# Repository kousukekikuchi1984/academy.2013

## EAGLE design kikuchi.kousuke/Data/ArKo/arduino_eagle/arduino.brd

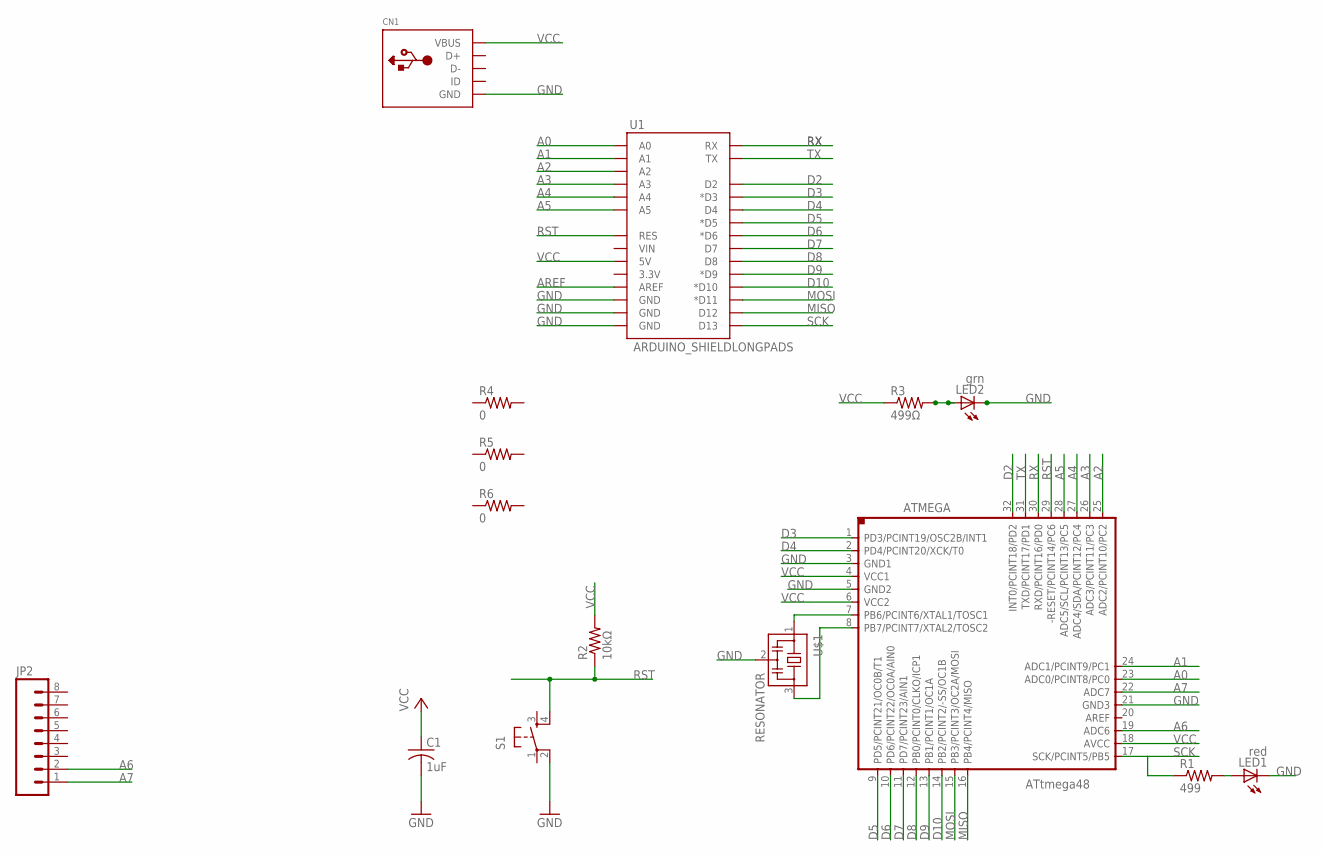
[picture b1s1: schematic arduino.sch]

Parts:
ATMEGA: 328p-au; TQFP32-08
C1: 1uF; C1206
CN1: USBMINIB; USB-MINIB
JP2: M08LOCK_LONGPADS; 1X08_LOCK_LONGPADS
LED1: red; CHIPLED_1206
LED2: grn; CHIPLED_1206
R1: 499; R1206
R2: 10kΩ; M1206
R3: 499Ω; M1206
R4, R5, R6: 0; M1206
S1: 6MM_SWITCH6MM_SWITCH; 6MM_SWITCH
U1: ARDUINO_SHIELDLONGPADS; DUEMILANOVE_SHIELD_LONGPADS
U$1: RESONATOR; EFOBM

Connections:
A0: ATMEGA.23 (ADC0/PCINT8/PC0), U1.A0
A1: ATMEGA.24 (ADC1/PCINT9/PC1), U1.A1
A2: ATMEGA.25 (ADC2/PCINT10/PC2), U1.A2
A3: ATMEGA.26 (ADC3/PCINT11/PC3), U1.A3
A4: ATMEGA.27 (ADC4/SDA/PCINT12/PC4), U1.A4
A5: ATMEGA.28 (ADC5/SCL/PCINT13/PC5), U1.A5
A6: ATMEGA.19 (ADC6), JP2.2
A7: ATMEGA.22 (ADC7), JP2.1
AREF: U1.AREF
D2: ATMEGA.32 (INT0/PCINT18/PD2), U1.D2
D3: ATMEGA.1 (PD3/PCINT19/OSC2B/INT1), U1.D3 (*D3)
D4: ATMEGA.2 (PD4/PCINT20/XCK/T0), U1.D4
D5: ATMEGA.9 (PD5/PCINT21/OC0B/T1), U1.D5 (*D5)
D6: ATMEGA.10 (PD6/PCINT22/OC0A/AIN0), U1.D6 (*D6)
D7: ATMEGA.11 (PD7/PCINT23/AIN1), U1.D7
D8: ATMEGA.12 (PB0/PCINT0/CLKO/ICP1), U1.D8
D9: ATMEGA.13 (PB1/PCINT1/OC1A), U1.D9 (*D9)
D10: ATMEGA.14 (PB2/PCINT2/-SS/OC1B), U1.D10 (*D10)
GND: ATMEGA.3 (GND1), ATMEGA.5 (GND2), ATMEGA.21 (GND3), C1.2, CN1.GND, LED1.C, LED2.C, S1.2 (P1), U1.GND@0 (GND), U1.GND@1 (GND), U1.GND@2 (GND), U$1.2
MISO: ATMEGA.16 (PB4/PCINT4/MISO), U1.D12
MOSI: ATMEGA.15 (PB3/PCINT3/OC2A/MOSI), U1.D11 (*D11)
unnamed: LED1.A, R1.2
unnamed: ATMEGA.7 (PB6/PCINT6/XTAL1/TOSC1), U$1.1
unnamed: ATMEGA.8 (PB7/PCINT7/XTAL2/TOSC2), U$1.3
unnamed: LED2.A, R3.2
RST: ATMEGA.29 (-RESET/PCINT14/PC6), R2.1, S1.4 (S1), U1.RES
RX: ATMEGA.30 (RXD/PCINT16/PD0), U1.RX
SCK: ATMEGA.17 (SCK/PCINT5/PB5), R1.1, U1.D13
TX: ATMEGA.31 (TXD/PCINT17/PD1), U1.TX
VCC: ATMEGA.4 (VCC1), ATMEGA.6 (VCC2), ATMEGA.18 (AVCC), C1.1, CN1.VBUS, R2.2, R3.1, U1.5V

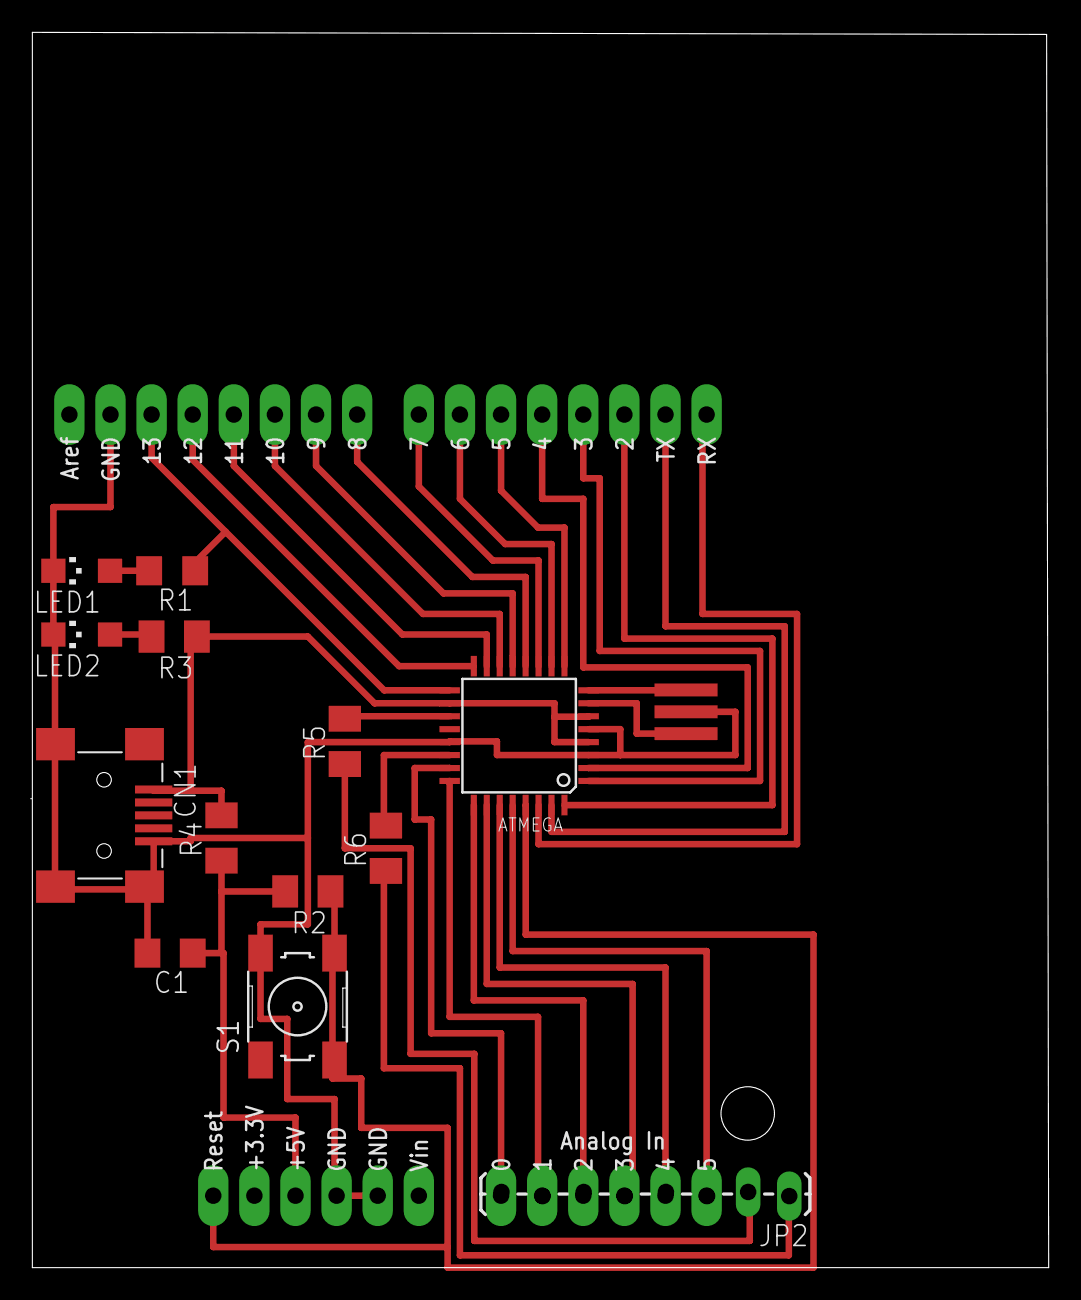
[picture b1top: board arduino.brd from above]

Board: 2 copper layers, 62.8 x 76.3 mm, 15 parts (0 on the bottom side), 29 nets.

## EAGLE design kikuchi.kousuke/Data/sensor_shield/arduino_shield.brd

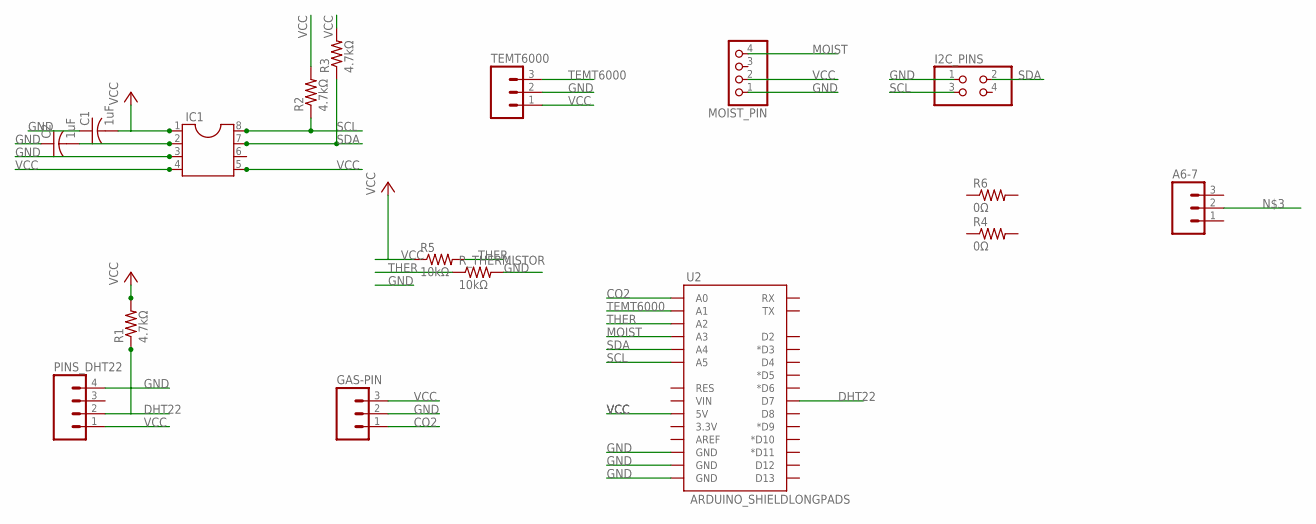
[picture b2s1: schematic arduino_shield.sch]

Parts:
A6-7: M03LOCK_LONGPADS; 1X03_LOCK_LONGPADS
C1, C2: 1uF; C1206
GAS-PIN: M03LOCK_LONGPADS; 1X03_LOCK_LONGPADS
I2C_PINS: PINHD-2X2; 2X02
IC1: DIL8S; SOCKET-08
MOIST_PIN: PINHD-1X4M; 1X04M
PINS_DHT22: M04LOCK_LONGPADS; 1X04_LOCK_LONGPADS
R1, R2, R3: 4.7kΩ; M1206
R4, R6: 0Ω; M1206
R5: 10kΩ; M1206
R_THERMISTOR: 10kΩ; M1206
TEMT6000: M03LOCK_LONGPADS; 1X03_LOCK_LONGPADS
U2: ARDUINO_SHIELDLONGPADS; DUEMILANOVE_SHIELD_LONGPADS

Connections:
CO2: GAS-PIN.1, U2.A0
DHT22: PINS_DHT22.2, R1.1, U2.D7
GND: C1.1, C2.1, GAS-PIN.2, I2C_PINS.1, IC1.3, MOIST_PIN.1, PINS_DHT22.4, R_THERMISTOR.2, TEMT6000.2, U2.GND@0 (GND), U2.GND@1 (GND), U2.GND@2 (GND)
MOIST: MOIST_PIN.4, U2.A3
unnamed: C2.2, IC1.2
SCL: I2C_PINS.3, IC1.8, R2.1, U2.A5
SDA: I2C_PINS.2, IC1.7, R3.1, U2.A4
TEMT6000: TEMT6000.3, U2.A1
THER: R5.2, R_THERMISTOR.1, U2.A2
VCC: C1.2, GAS-PIN.3, IC1.1, IC1.4, IC1.5, MOIST_PIN.2, PINS_DHT22.1, R1.2, R2.2, R3.2, R5.1, TEMT6000.1, U2.5V

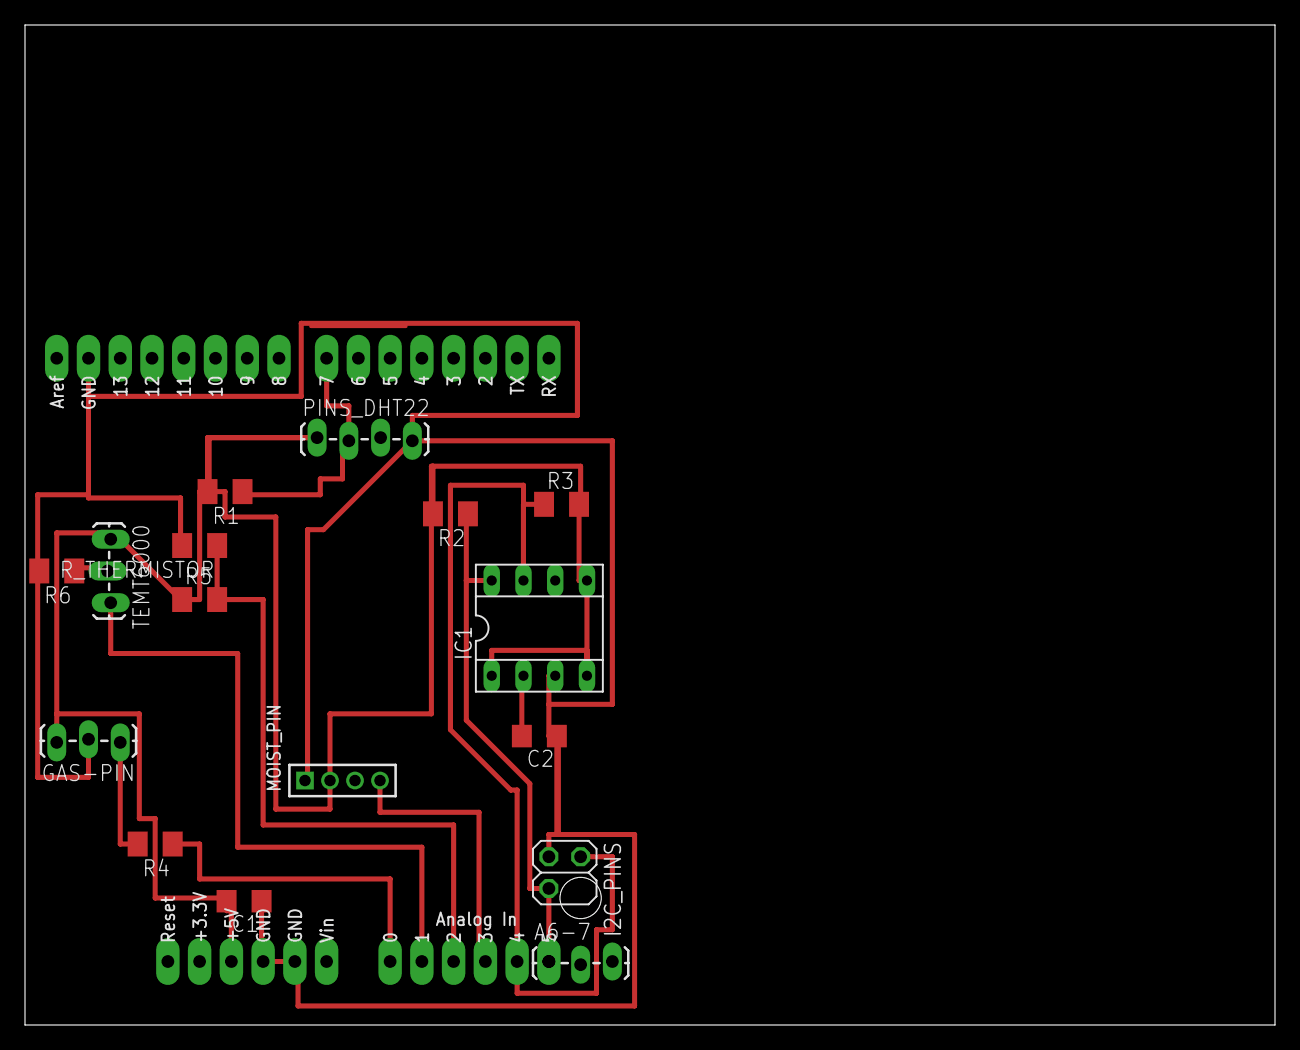
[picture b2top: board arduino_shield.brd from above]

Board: 2 copper layers, 100.0 x 80.0 mm, 17 parts (0 on the bottom side), 10 nets.

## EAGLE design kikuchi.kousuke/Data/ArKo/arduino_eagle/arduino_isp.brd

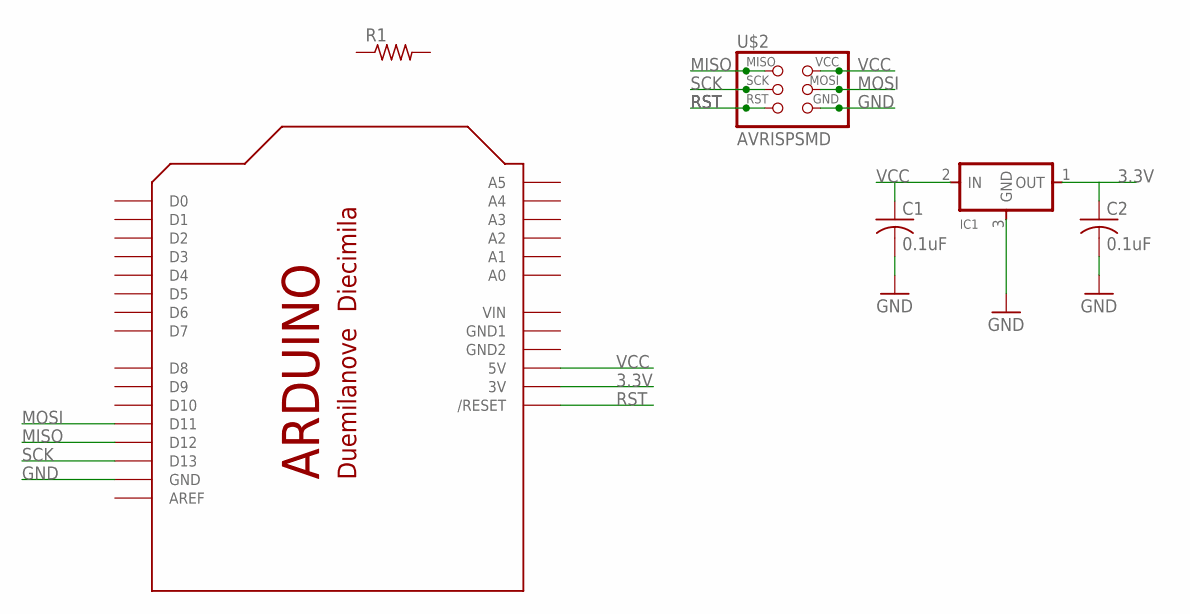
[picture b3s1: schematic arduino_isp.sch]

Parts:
C1, C2: 0.1uF; C1206
IC1: REGULATORSOT23; SOT23
R1: R-US_M1206; M1206
U$1: ARDUINODUEMILANOVE; ARDUINO
U$2: AVRISPSMD; 2X03SMD

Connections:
3.3V: C2.1, IC1.1 (OUT), U$1.3V
GND: C1.2, C2.2, IC1.3 (GND), U$1.GND, U$2.6 (GND)
GND1: U$1.GND1
GND2: U$1.GND2
MISO: U$1.D12, U$2.1 (MISO)
MOSI: U$1.D11, U$2.4 (MOSI)
RST: U$1.RESET (/RESET), U$2.5 (RST)
SCK: U$1.D13, U$2.3 (SCK)
VCC: C1.1, IC1.2 (IN), U$1.5V, U$2.2 (VCC)
VIN: U$1.VIN

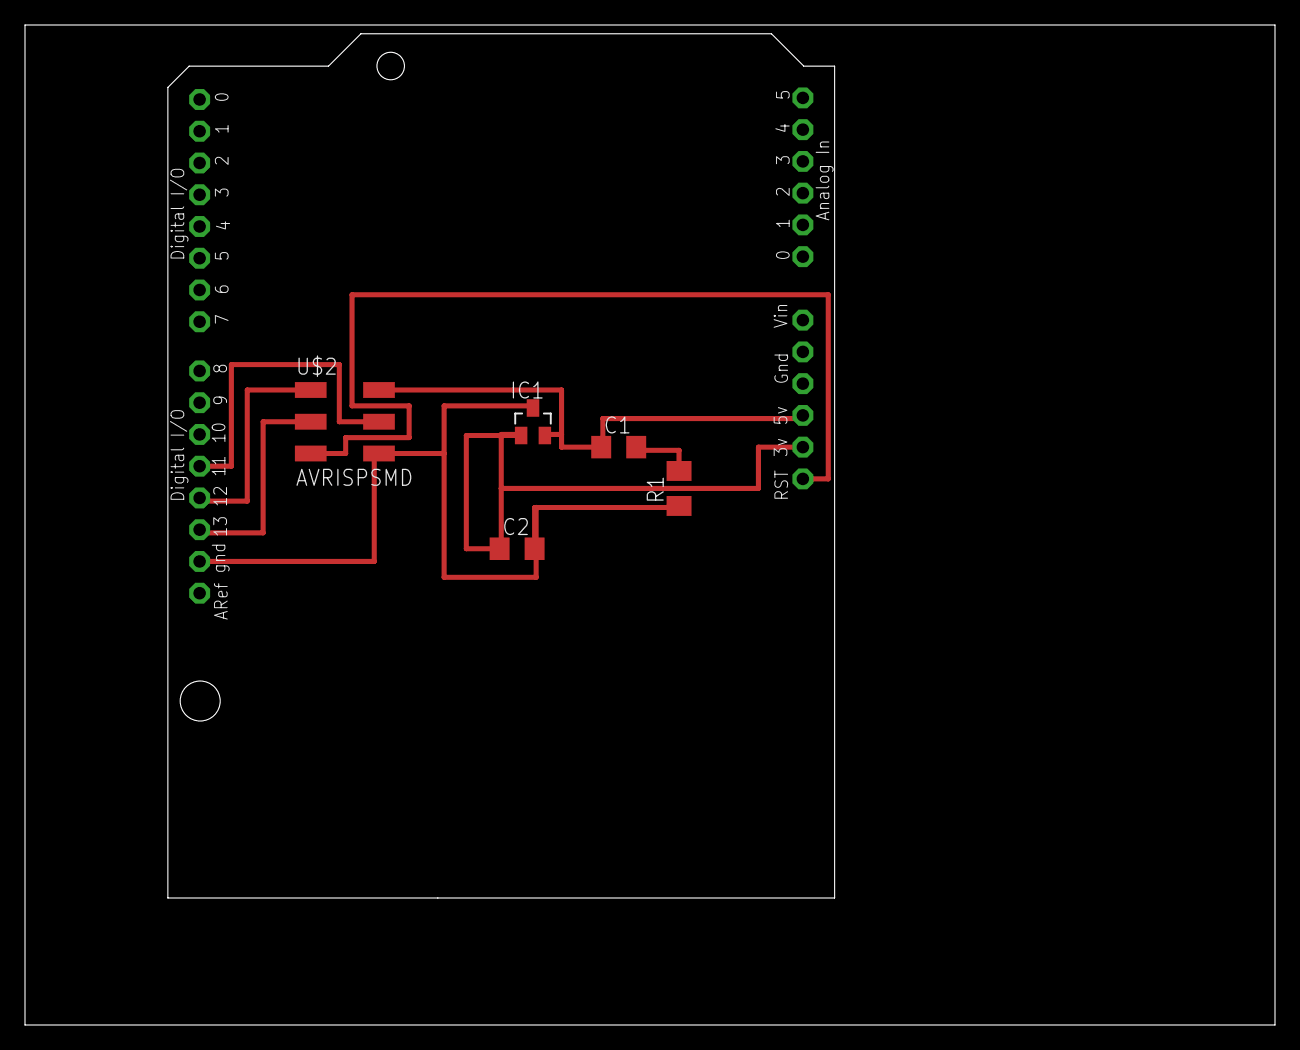
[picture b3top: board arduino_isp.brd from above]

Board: 2 copper layers, 100.0 x 80.0 mm, 6 parts (0 on the bottom side), 7 nets.

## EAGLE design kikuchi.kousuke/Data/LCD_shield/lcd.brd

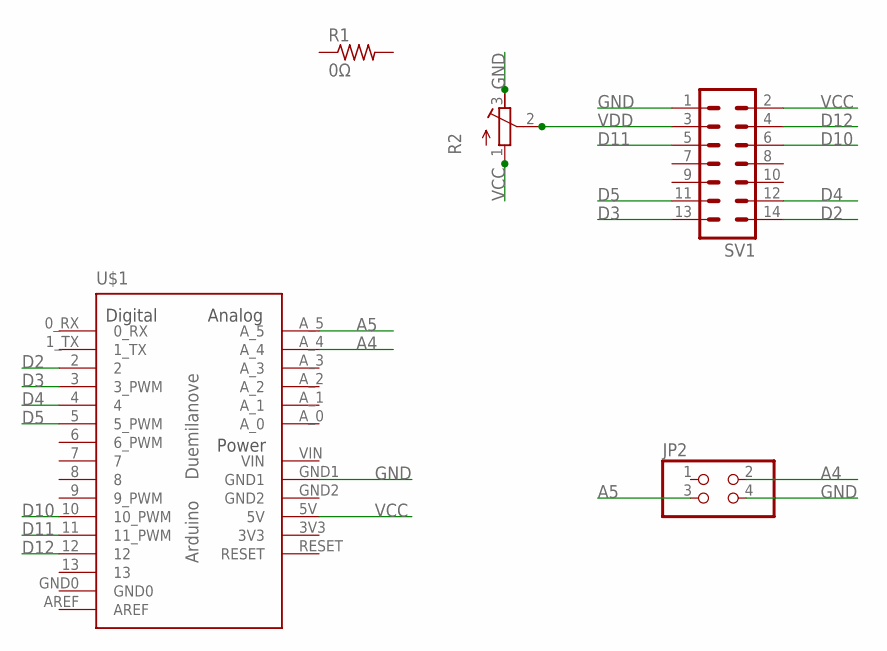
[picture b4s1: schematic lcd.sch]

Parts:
JP2: PINHD-2X2; 2X02
R1: 0Ω; M1206
R2: R-TRIMM5W; RTRIM5W
SV1: MA07-2
U$1: ARDUINO-USBLONG_PADS_TEXT; SHIELD

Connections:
3V3: U$1.3V3
A4: JP2.2, U$1.A_4
A5: JP2.3, U$1.A_5
D2: SV1.14, U$1.2
D3: SV1.13, U$1.3 (3_PWM)
D4: SV1.12, U$1.4
D5: SV1.11, U$1.5 (5_PWM)
D10: SV1.6, U$1.10 (10_PWM)
D11: SV1.5, U$1.11 (11_PWM)
D12: SV1.4, U$1.12
GND: JP2.4, R2.3 (E), SV1.1, U$1.GND1
VCC: R2.1 (A), SV1.2, U$1.5V
VDD: R2.2 (S), SV1.3
VIN: U$1.VIN

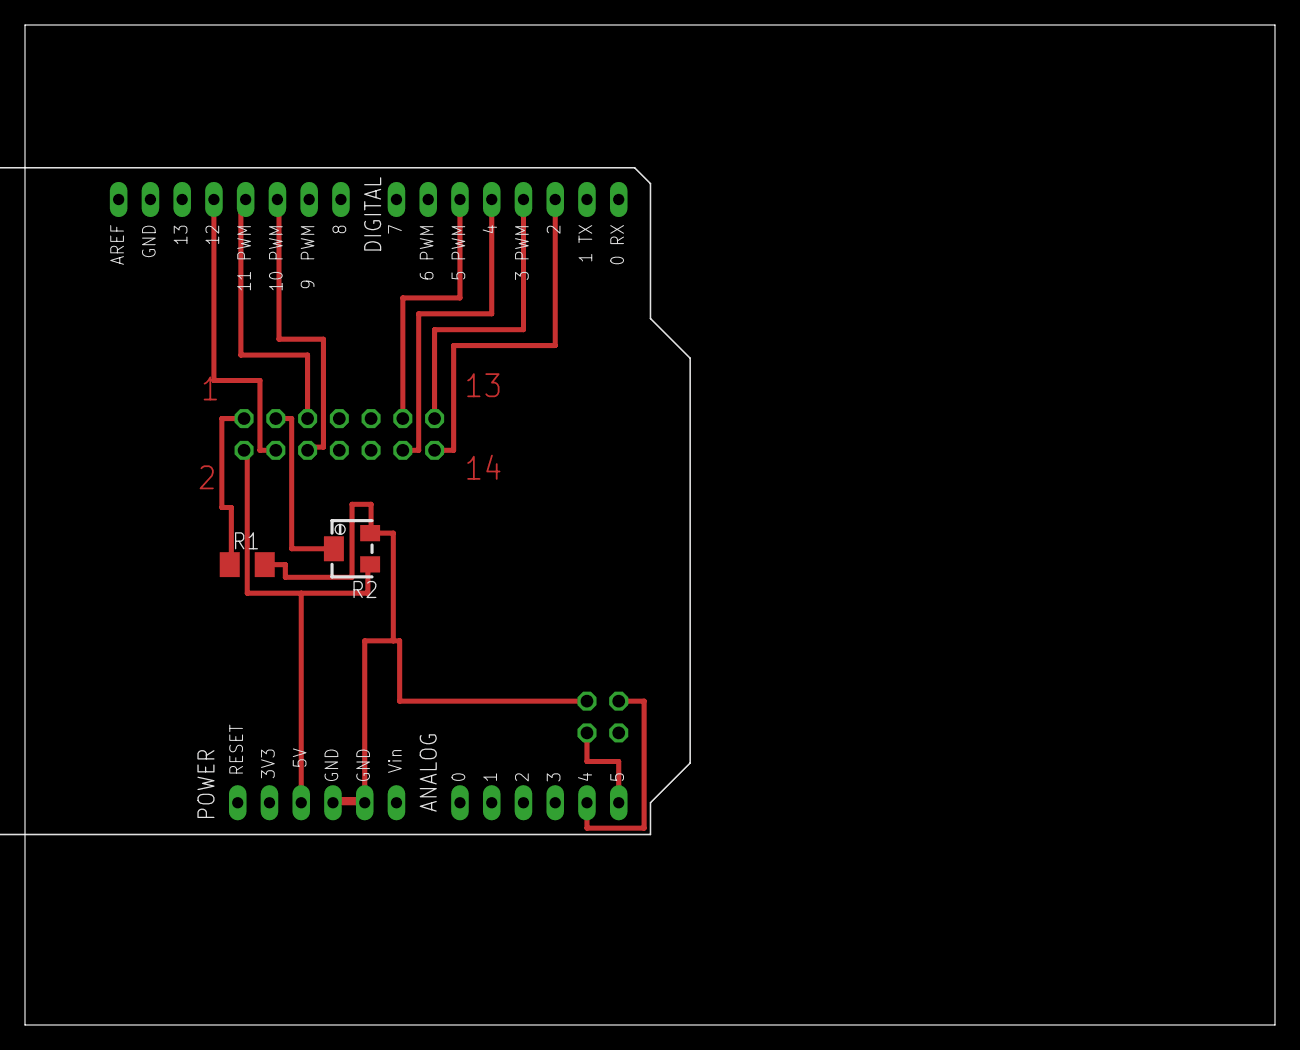
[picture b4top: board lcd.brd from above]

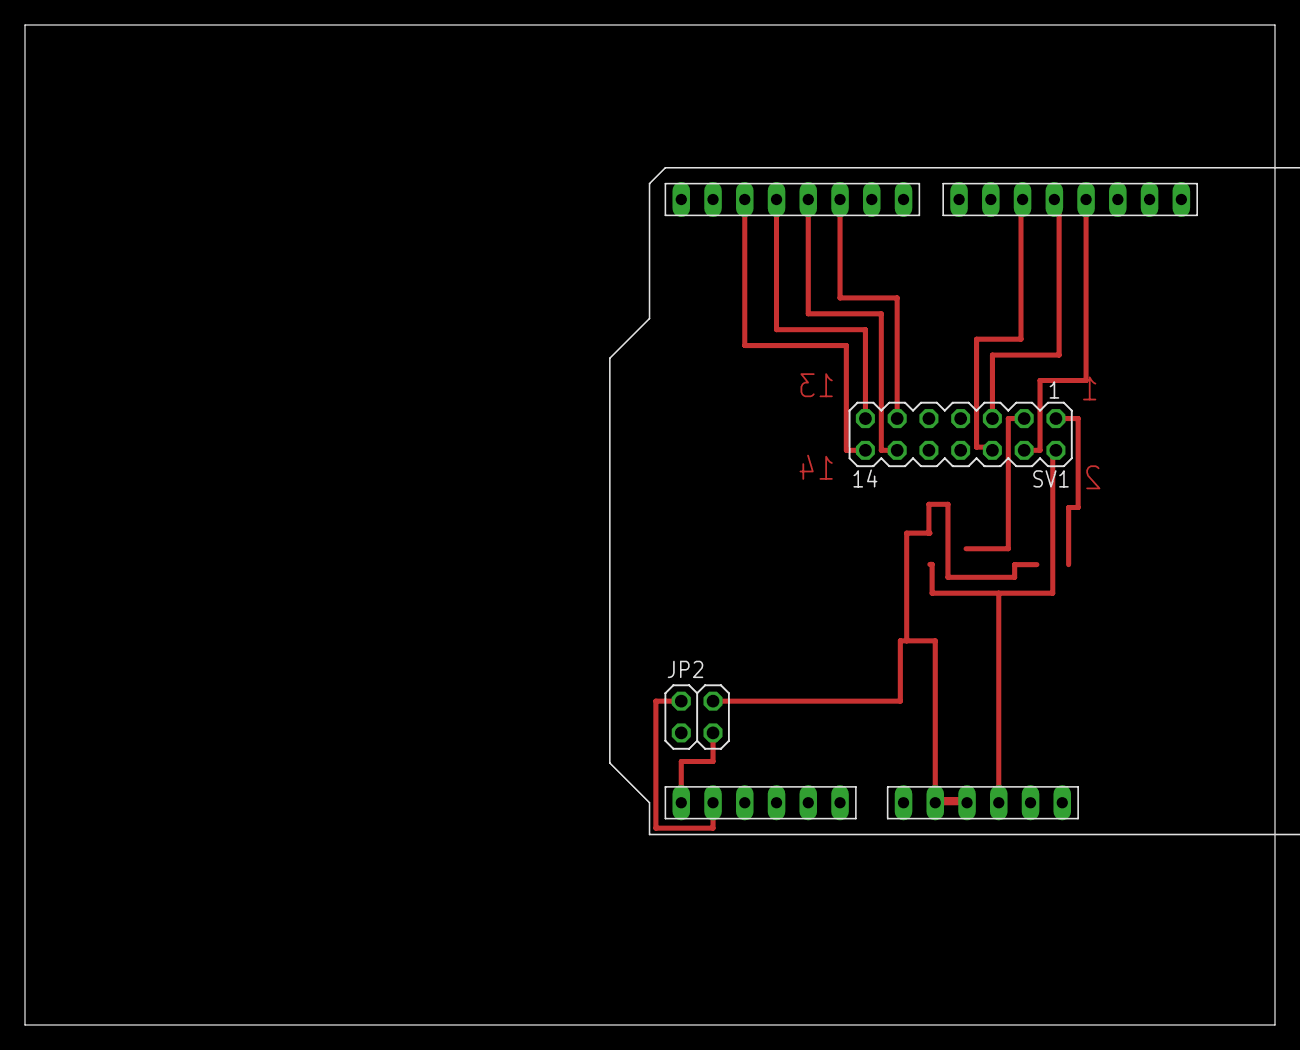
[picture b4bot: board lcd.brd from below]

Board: 2 copper layers, 100.0 x 80.0 mm, 5 parts (2 on the bottom side), 12 nets.

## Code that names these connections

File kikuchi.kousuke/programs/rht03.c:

#include <avr/io.h>
#include <util/delay.h>
#include <avr/interrupt.h>
#include <stdio.h>
#include <stdlib.h>
#include <math.h>

unsigned int seg[6];
unsigned int mx;

#define cbi(addr, bit)     addr &= ~(1<<bit)
#define sbi(addr, bit)     addr |=  (1<<bit)

// milisecond order delay
void delay_ms(unsigned int t)
{
    while(t--)
        _delay_ms(1);
}

// Returns mask 7-seg. display
unsigned int mask(unsigned int num) {
      switch (num) {
        case 0 : return 0xa0;
        case 1 : return 0xfc;
        case 2 : return 0xc1;
        case 3 : return 0xd0;
        case 4 : return 0x9c;
        case 5 : return 0x92;
        case 6 : return 0x82;
        case 7 : return 0xf8;
        case 8 : return 0x80;
        case 9 : return 0x90;
        case 10 : return 0xdf;  // -
        case 11 : return 0x83;    // E
        case 12 : return 0xcf;    // r
        case 99 : return 0xff;     // space
        default: return 0xfe;
    }
}

// Timer1 Overflow interrupt
ISR(TIMER1_OVF_vect)
{
    TCNT1 = 128;
    PORTA = seg[mx];
    switch(mx) {
        case 0: PORTB = ~_BV(PB6); break;
        case 1: PORTB = ~_BV(PB5); break; 
        case 2: PORTB = ~_BV(PB3); break;
        case 3: PORTB = ~_BV(PB2); break;
        case 4: PORTB = ~_BV(PB1); break; 
        case 5: PORTB = ~_BV(PB0); break;
    }
    mx++;
    if(mx > 5)
        mx = 0;
}

// read 1-wire sensor DHT22(RHT03)
void dht22_read(int *temp, int *humd)
{
    unsigned int i, j;
    unsigned char rs[5];
    unsigned int c;

    cli();

    // Host send start signal
    sbi(DDRA, DDA7);    // PA7 output
    cbi(PORTA, PA7);    // PA7 low
    delay_ms(1);
    // Host pull up and wait for sensor response
    cbi(DDRA, DDA7);    // PA7 input

    _delay_us(20);    // このディレイは最適化できていません。
    loop_until_bit_is_clear(PINA, PINA7);     // wait sensor send out response(20-40us)
    loop_until_bit_is_set(PINA, PINA7);        // wait sensor pull up get ready(80us)
    loop_until_bit_is_clear(PINA, PINA7);    // wait sensor send data(80us)

    // 40bit recive data 
    for(i = 0; i < 5; i++) {
           for(j = 0; j < 8; j++) {
            c = 0;
            loop_until_bit_is_set(PINA, PINA7);
            while(bit_is_set(PINA, PINA7)) {
                c++;
                _delay_us(1);
            }
            rs[i] <<= 1;
            if(c > 40)        // over 40count is "1"
                       rs[i] |= 1;
        }
    }

    sei();

    // check sum and value set
    if((rs[0] + rs[1] + rs[2] + rs[3] & 0xff) == rs[4]) {
        *humd = (rs[0] << 8 | rs[1]);
        *temp = (rs[2] << 8 | rs[3]);        // 室内での利用なので氷点下には対応しない
    } else {
        *humd = 1000;    //　エラー表示のための適当な値
        *temp = 1000;
    }
}

int main(void)
{
    unsigned int i;
    int tem, hum;

     DDRA = 0b01111111;        // PA0-6 7seg cathode, PA7 DHT22 1-wire
    DDRB = 0b11111111;        // 7seg Anode control

    TCNT1 = 128;             // Timer1 counter set
    TCCR1A= 0;                // Timer1 standard timer mode                
    TCCR1B= 8;                // Timer1 prescaler 1/128
    TIMSK = _BV(TOIE1);        // Timer1 Overflow Interrupt Enable

    delay_ms(2000);
    sei();

    while(1) {

        dht22_read(&tem, &hum);

        if(tem > 500 || tem < -99) {        // 表示は氷点下9.9℃まで対応している
            seg[0] = mask(11);
            seg[1] = mask(12);
            seg[2] = mask(12);
        } else {
            if(tem < 0) {
                seg[0] = mask(10);
            } else {
                i = (tem / 100) % 10;
                if(i == 0)
                    i = 99;
                seg[0] = mask(i);
            }
            i = abs((tem / 10) % 10);
            seg[1] = mask(i);
            i = abs(tem % 10);
            seg[2] = mask(i);
        }
        if(hum > 999 || hum < 0) {    // 湿度100%はありうるのでこれはマズイな。
            seg[3] = mask(11);
            seg[4] = mask(12);
            seg[5] = mask(12);
        } else {
            i = (hum / 100) % 10;
            if(i == 0)
                i = 99;
            seg[3] = mask(i);
            i = (hum / 10) % 10;
            seg[4] = mask(i);
            i = hum % 10;
            seg[5] = mask(i);
        }
        delay_ms(2000);    // DHT22での測定は2秒間隔
    }
}

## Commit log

2016-01-23 add all files

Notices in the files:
parts and their libraries:
01_SparkFun: Licensing: CC v3.0 Share-Alike You are welcome to use this library for commercial purposes.
